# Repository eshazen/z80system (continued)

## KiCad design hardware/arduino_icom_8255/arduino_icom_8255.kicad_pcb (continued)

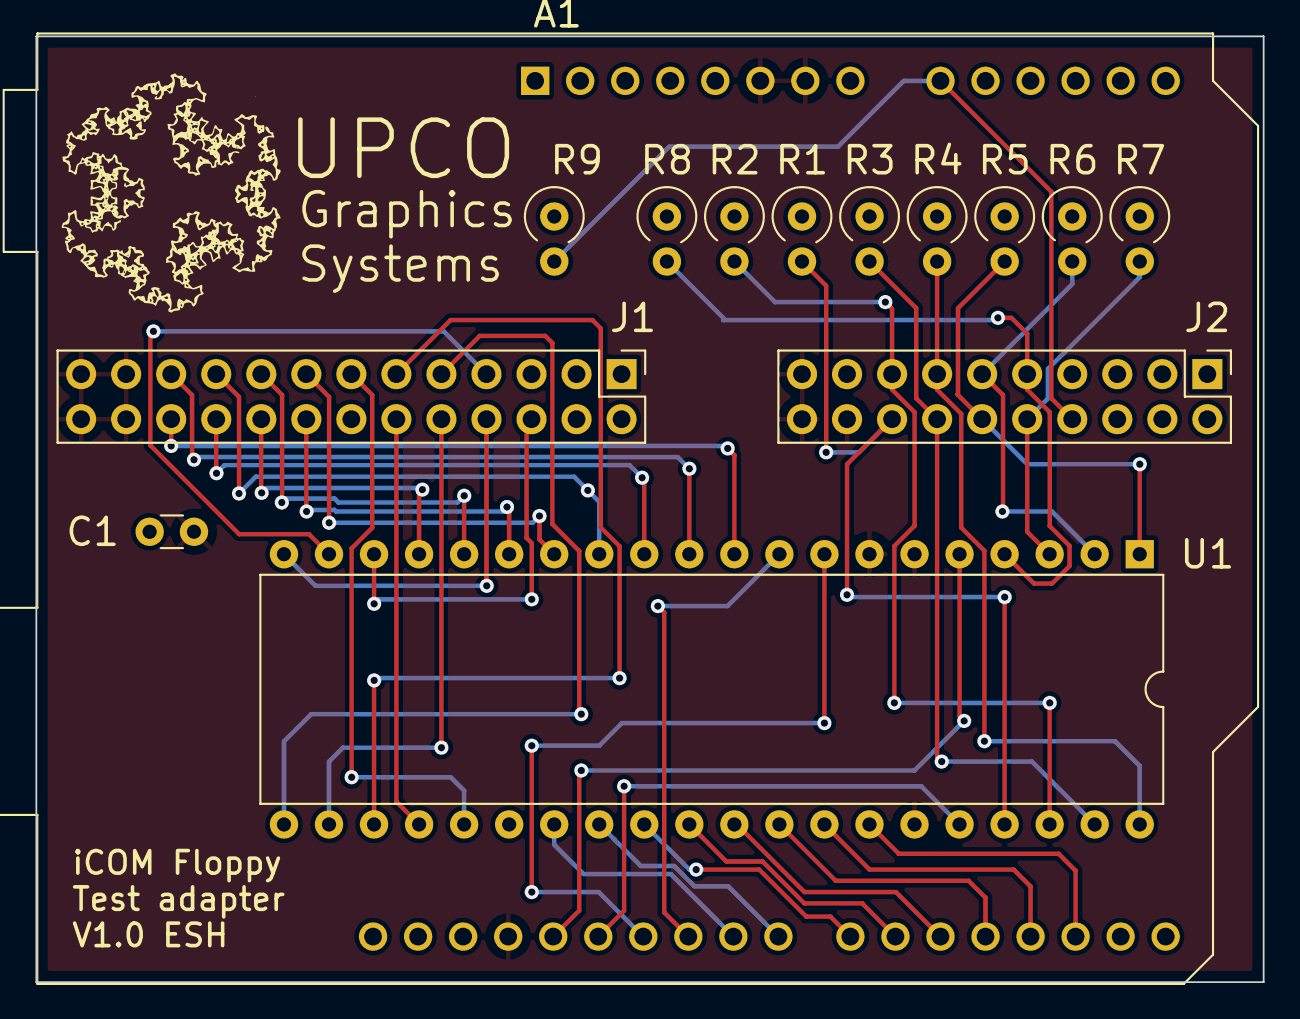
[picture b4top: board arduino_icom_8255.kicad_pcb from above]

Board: 2 copper layers, 69.2 x 53.3 mm, 14 parts (0 on the bottom side), 39 nets.

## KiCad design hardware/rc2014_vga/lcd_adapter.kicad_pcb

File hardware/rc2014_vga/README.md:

# LCD/VGA adapter for Digilent CMOD A7

This is a new RC2014 board which provides VGA display.
It can connect either to a surplus VGA LCD via flex connector
or standard VGA.

RC2014 interface via serial, with 6 pin connector for
a serial keyboard.

A possible PS/2 keyboard interface.

_Rev A Errors_

The VGA connector overlaps several resistors and C2.  This is salvageable
by either cutting away part of the VGA or mounting the other parts on the back.

It turns out that the CMOD-A7 has a built-in oscillator, so the oscillator module
and 3.3V regulator aren't needed at all, so I left them out.

Also it is *highly recommended* to put a Schottky diode in series with the power
to the CMOD-A7 so you can freely use either USB power or RC2014 power.
Plus the CMOD-A7 can take 5V directly.  I cut the trace to pin 24 of the CMOD
and soldered a diode from 5V to this pin.

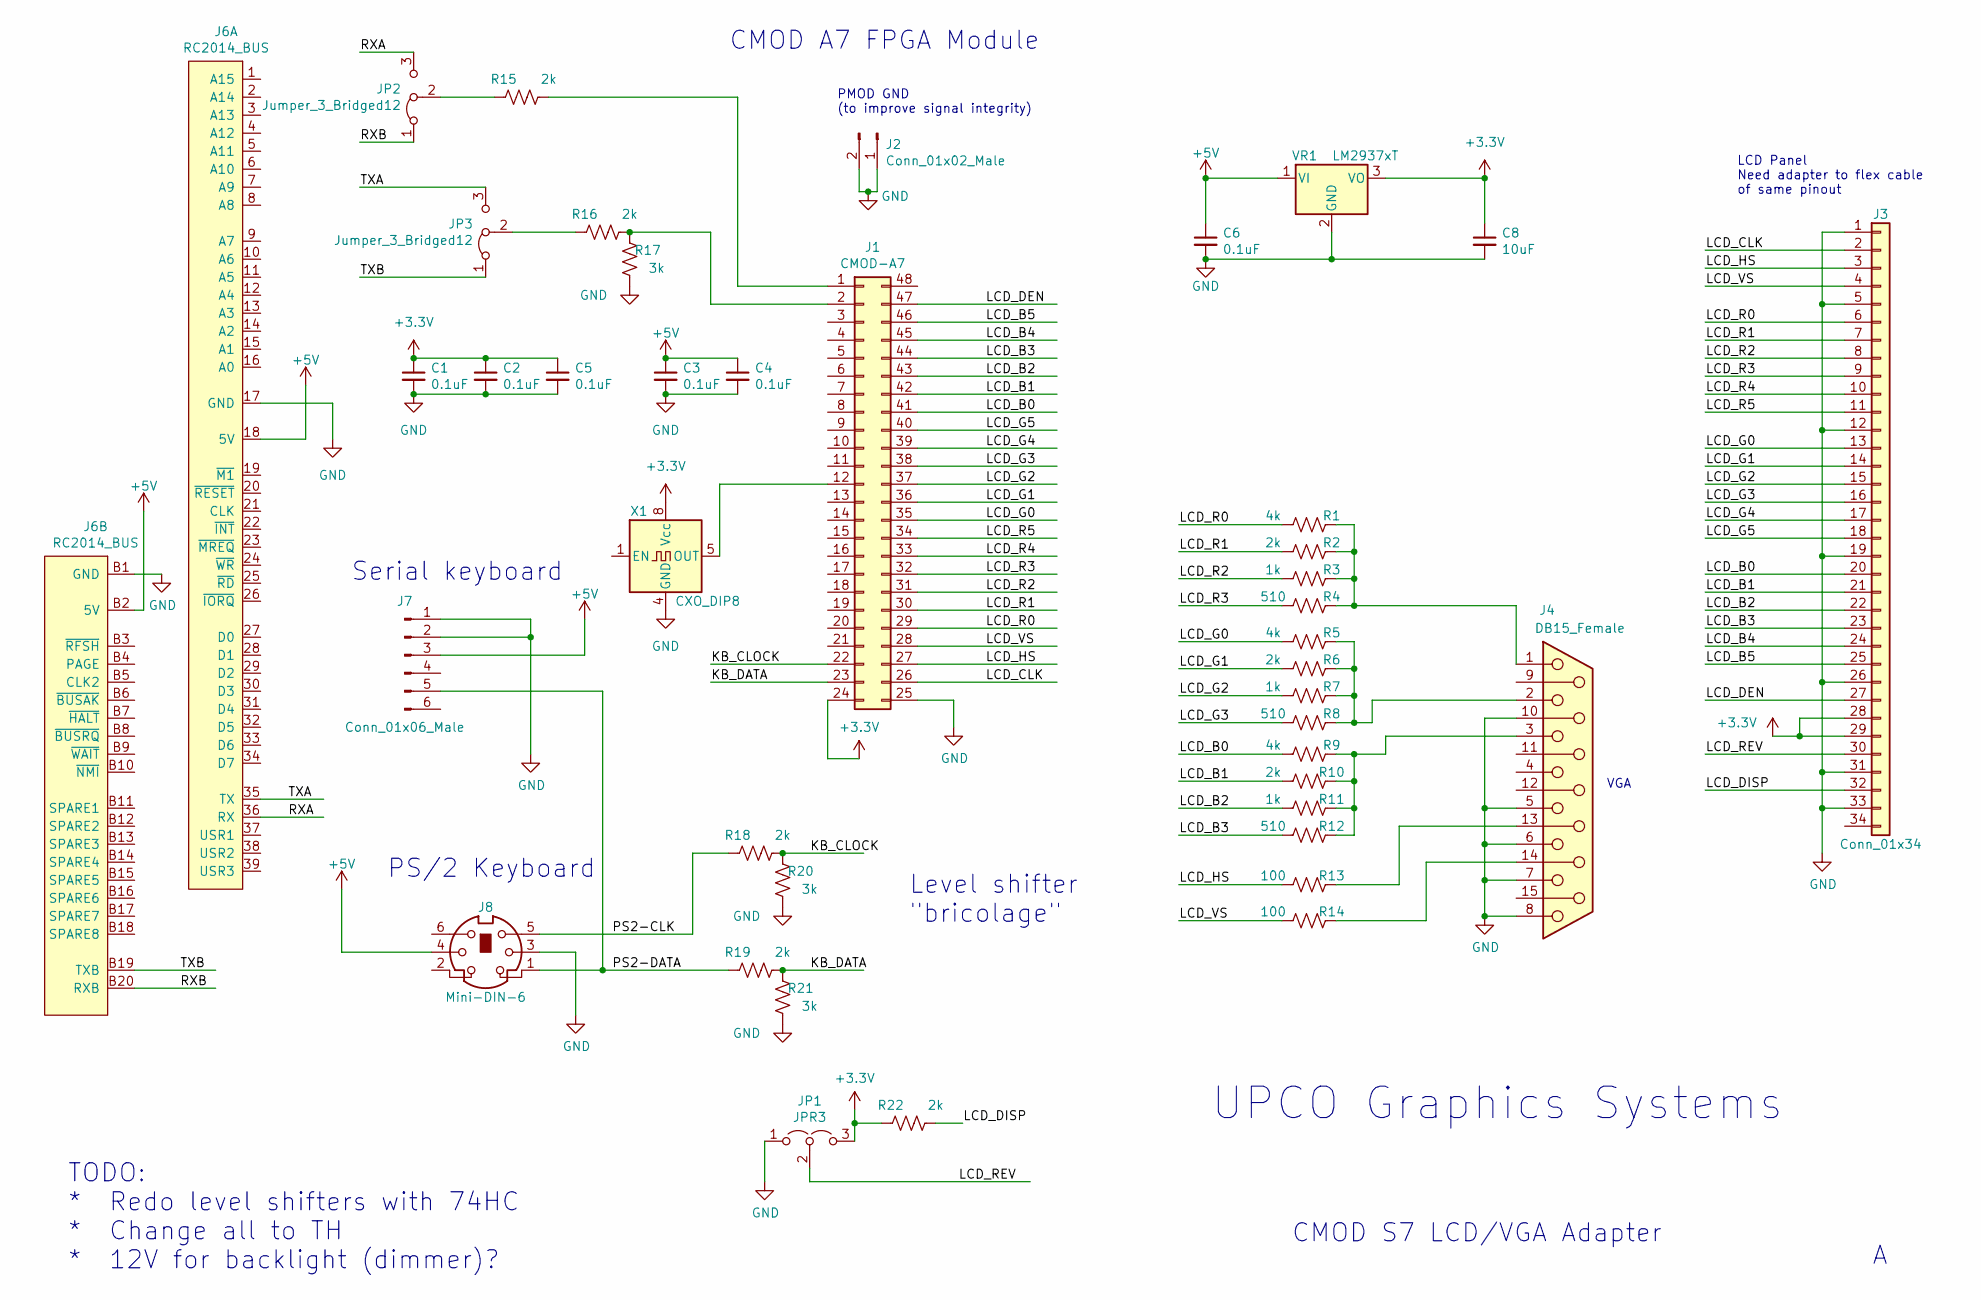
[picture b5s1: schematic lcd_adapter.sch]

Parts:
C1, C2, C3, C4, C5, C6: 0.1uF; C_Disc_D5.0mm_W2.5mm_P2.50mm
C8: 10uF; C_Disc_D5.0mm_W2.5mm_P2.50mm
J1: CMOD-A7; DIP-48_W15.24mm_Socket_LongPads
J2: Conn_01x02_Male; PinHeader_2x01_P2.54mm_Vertical
J3: Conn_01x34; PinHeader_2x17_P2.54mm_Vertical
J4: DB15_Female; DSUB-15-HD_Female_Horizontal_P2.29x1.98mm_EdgePinOffset9.40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
J6: RC2014_BUS; RC2014_Header
J7: Conn_01x06_Male; PinHeader_1x06_P2.54mm_Vertical
J8: Mini-DIN-6; PinSocket_2x03_P2.54mm_Vertical
JP1: JPR3; PinHeader_1x03_P2.54mm_Vertical
JP2, JP3: Jumper_3_Bridged12; PinSocket_1x03_P2.54mm_Vertical
R1, R5, R9: 4k; R_Axial_DIN0204_L3.6mm_D1.6mm_P2.54mm_Vertical
R2, R6, R10, R15, R16, R18, R19, R22: 2k; R_Axial_DIN0204_L3.6mm_D1.6mm_P2.54mm_Vertical
R3, R7, R11: 1k; R_Axial_DIN0204_L3.6mm_D1.6mm_P2.54mm_Vertical
R4, R8, R12: 510; R_Axial_DIN0204_L3.6mm_D1.6mm_P2.54mm_Vertical
R13, R14: 100; R_Axial_DIN0204_L3.6mm_D1.6mm_P2.54mm_Vertical
R17, R20, R21: 3k; R_Axial_DIN0204_L3.6mm_D1.6mm_P2.54mm_Vertical
VR1: LM2937xT; TO-220-3_Vertical
X1: CXO_DIP8; Oscillator_DIP-8

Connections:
+3V3: C1.1, C2.1, C5.1, C8.1, J1.24, J3.28, J3.29, JP1.3 (B), R22.2, VR1.3 (VO), X1.8 (Vcc)
+5V: C3.1, C4.1, C6.1, J6.18 (5V), J6.B2 (5V), J7.3, J8.4, VR1.1 (VI)
/KB_CLOCK: J1.22, R18.1, R20.2
/KB_DATA: J1.23, R19.1, R21.2
/LCD_B0: J1.41, J3.20, R9.2
/LCD_B1: J1.42, J3.21, R10.2
/LCD_B2: J1.43, J3.22, R11.2
/LCD_B3: J1.44, J3.23, R12.2
/LCD_B4: J1.45, J3.24
/LCD_B5: J1.46, J3.25
/LCD_CLK: J1.26, J3.2
/LCD_DEN: J1.47, J3.27
/LCD_DISP: J3.32, R22.1
/LCD_G0: J1.35, J3.13, R5.2
/LCD_G1: J1.36, J3.14, R6.2
/LCD_G2: J1.37, J3.15, R7.2
/LCD_G3: J1.38, J3.16, R8.2
/LCD_G4: J1.39, J3.17
/LCD_G5: J1.40, J3.18
/LCD_HS: J1.27, J3.3, R13.2
/LCD_R0: J1.29, J3.6, R1.2
/LCD_R1: J1.30, J3.7, R2.2
/LCD_R2: J1.31, J3.8, R3.2
/LCD_R3: J1.32, J3.9, R4.2
/LCD_R4: J1.33, J3.10
/LCD_R5: J1.34, J3.11
/LCD_REV: J3.30, JP1.2 (C)
/LCD_VS: J1.28, J3.4, R14.2
/PS2-CLK: J8.5, R18.2
/PS2-DATA: J7.5, J8.1, R19.2
/RXA: J6.36 (RX), JP2.3 (B)
/RXB: J6.B20 (RXB), JP2.1 (A)
/TXA: J6.35 (TX), JP3.3 (B)
/TXB: J6.B19 (TXB), JP3.1 (A)
GND: C1.2, C2.2, C3.2, C4.2, C5.2, C6.2, C8.2, J1.25, J2.1, J2.2, J3.1, J3.5, J3.12, J3.19, J3.26, J3.31, J3.33, J4.5, J4.6, J4.7, J4.8, J4.10, J6.17 (GND), J6.B1 (GND), J7.1, J7.2, J8.3, JP1.1 (A), R17.1, R20.1, R21.1, VR1.2 (GND), X1.4 (GND)
unnamed: J1.1, R15.1
unnamed: J1.2, R16.1, R17.2
unnamed: J1.12, X1.5 (OUT)
unnamed: J4.1, R1.1, R2.1, R3.1, R4.1
unnamed: J4.2, R5.1, R6.1, R7.1, R8.1
unnamed: J4.3, R9.1, R10.1, R11.1, R12.1
unnamed: J4.13, R13.1
unnamed: J4.14, R14.1
unnamed: JP2.2 (C), R15.2
unnamed: JP3.2 (C), R16.2

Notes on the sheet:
PMOD GND (to improve signal integrity)
LCD Panel Need adapter to flex cable of same pinout
VGA
UPCO Graphics Systems
CMOD S7 LCD/VGA Adapter
TODO: * Redo level shifters with 74HC * Change all to TH * 12V for backlight (dimmer)?
CMOD A7 FPGA Module
Serial keyboard
PS/2 Keyboard
Level shifter "bricolage"

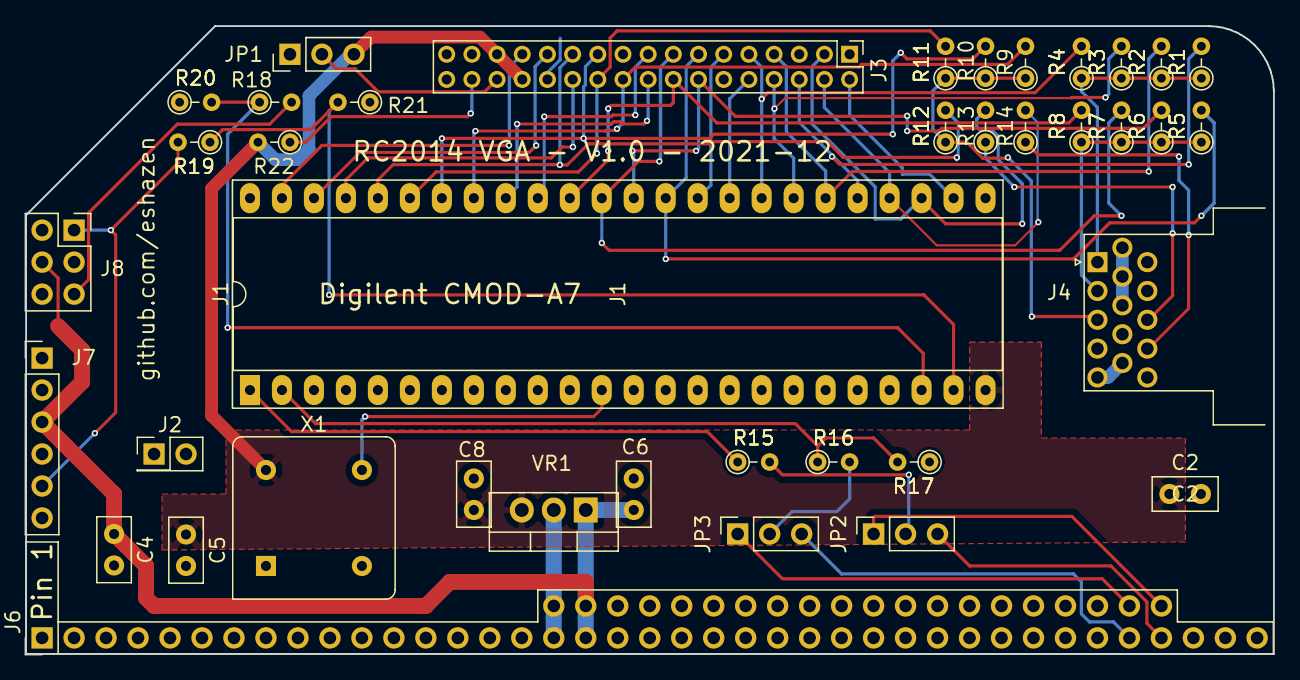
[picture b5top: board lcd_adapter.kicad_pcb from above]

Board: 2 copper layers, 99.1 x 49.9 mm, 39 parts (0 on the bottom side), 45 nets.

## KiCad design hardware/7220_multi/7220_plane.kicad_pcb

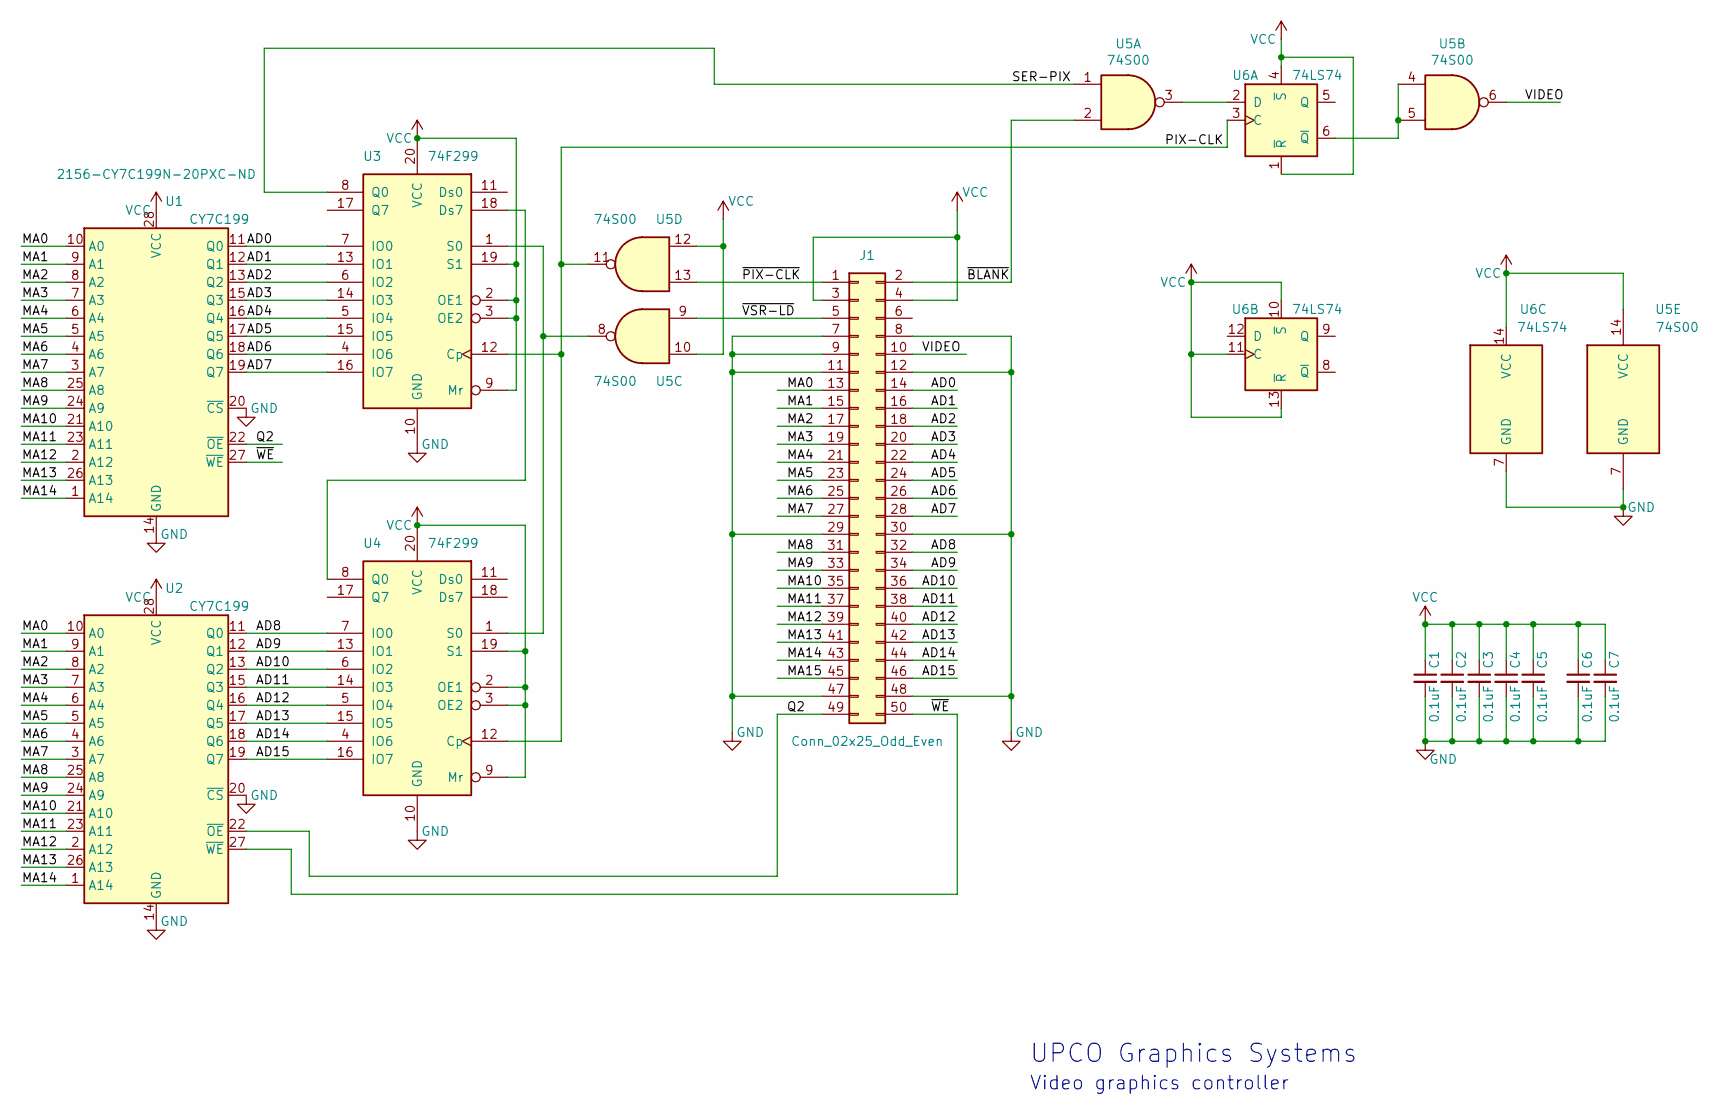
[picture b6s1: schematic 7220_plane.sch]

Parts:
C1, C2, C3, C4, C5, C6, C7: 0.1uF; C_Disc_D5.0mm_W2.5mm_P2.50mm
J1: Conn_02x25_Odd_Even; PinSocket_2x25_P2.54mm_Vertical
U1, U2: CY7C199; DIP-28_W7.62mm
U3, U4: 74F299; DIP-20_W7.62mm
U5: 74S00; DIP-14_W7.62mm
U6: 74LS74; DIP-14_W7.62mm

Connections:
/AD0: J1.14, U1.11 (Q0), U3.7 (IO0)
/AD1: J1.16, U1.12 (Q1), U3.13 (IO1)
/AD2: J1.18, U1.13 (Q2), U3.6 (IO2)
/AD3: J1.20, U1.15 (Q3), U3.14 (IO3)
/AD4: J1.22, U1.16 (Q4), U3.5 (IO4)
/AD5: J1.24, U1.17 (Q5), U3.15 (IO5)
/AD6: J1.26, U1.18 (Q6), U3.4 (IO6)
/AD7: J1.28, U1.19 (Q7), U3.16 (IO7)
/AD8: J1.32, U2.11 (Q0), U4.7 (IO0)
/AD9: J1.34, U2.12 (Q1), U4.13 (IO1)
/AD10: J1.36, U2.13 (Q2), U4.6 (IO2)
/AD11: J1.38, U2.15 (Q3), U4.14 (IO3)
/AD12: J1.40, U2.16 (Q4), U4.5 (IO4)
/AD13: J1.42, U2.17 (Q5), U4.15 (IO5)
/AD14: J1.44, U2.18 (Q6), U4.4 (IO6)
/AD15: J1.46, U2.19 (Q7), U4.16 (IO7)
/MA0: J1.13, U1.10 (A0), U2.10 (A0)
/MA1: J1.15, U1.9 (A1), U2.9 (A1)
/MA2: J1.17, U1.8 (A2), U2.8 (A2)
/MA3: J1.19, U1.7 (A3), U2.7 (A3)
/MA4: J1.21, U1.6 (A4), U2.6 (A4)
/MA5: J1.23, U1.5 (A5), U2.5 (A5)
/MA6: J1.25, U1.4 (A6), U2.4 (A6)
/MA7: J1.27, U1.3 (A7), U2.3 (A7)
/MA8: J1.31, U1.25 (A8), U2.25 (A8)
/MA9: J1.33, U1.24 (A9), U2.24 (A9)
/MA10: J1.35, U1.21 (A10), U2.21 (A10)
/MA11: J1.37, U1.23 (A11), U2.23 (A11)
/MA12: J1.39, U1.2 (A12), U2.2 (A12)
/MA13: J1.41, U1.26 (A13), U2.26 (A13)
/MA14: J1.43, U1.1 (A14), U2.1 (A14)
/MA15: J1.45
/PIX-CLK: U3.12 (Cp), U4.12 (Cp), U5.11, U6.3 (C)
/Q2: J1.49, U1.22 (~OE), U2.22 (~OE)
/SER-PIX: U3.8 (Q0), U5.1
/VIDEO: J1.10, U5.6
/~BLANK: J1.2, U5.2
/~PIX-CLK: J1.1, U5.13
/~VSR-LD: J1.5, U5.9
/~WE: J1.50, U1.27 (~WE), U2.27 (~WE)
GND: C1.2, C2.2, C3.2, C4.2, C5.2, C6.2, C7.2, J1.7, J1.8, J1.9, J1.11, J1.12, J1.29, J1.30, J1.47, J1.48, U1.14 (GND), U1.20 (~CS), U2.14 (GND), U2.20 (~CS), U3.10 (GND), U4.10 (GND), U5.7 (GND), U6.7 (GND)
unnamed: U3.1 (S0), U4.1 (S0), U5.8
unnamed: U3.18 (Ds7), U4.8 (Q0)
unnamed: U5.3, U6.2 (D)
unnamed: U5.4, U5.5, U6.6 (~Q)
VCC: C1.1, C2.1, C3.1, C4.1, C5.1, C6.1, C7.1, J1.3, J1.4, U1.28 (VCC), U2.28 (VCC), U3.2 (OE1), U3.3 (OE2), U3.9 (Mr), U3.19 (S1), U3.20 (VCC), U4.2 (OE1), U4.3 (OE2), U4.9 (Mr), U4.19 (S1), U4.20 (VCC), U5.10, U5.12, U5.14 (VCC), U6.1 (~R), U6.4 (~S), U6.10 (~S), U6.11 (C), U6.13 (~R), U6.14 (VCC)

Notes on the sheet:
UPCO Graphics Systems
Video graphics controller

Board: 2 copper layers, 14 parts (0 on the bottom side), 45 nets, no tracks yet.

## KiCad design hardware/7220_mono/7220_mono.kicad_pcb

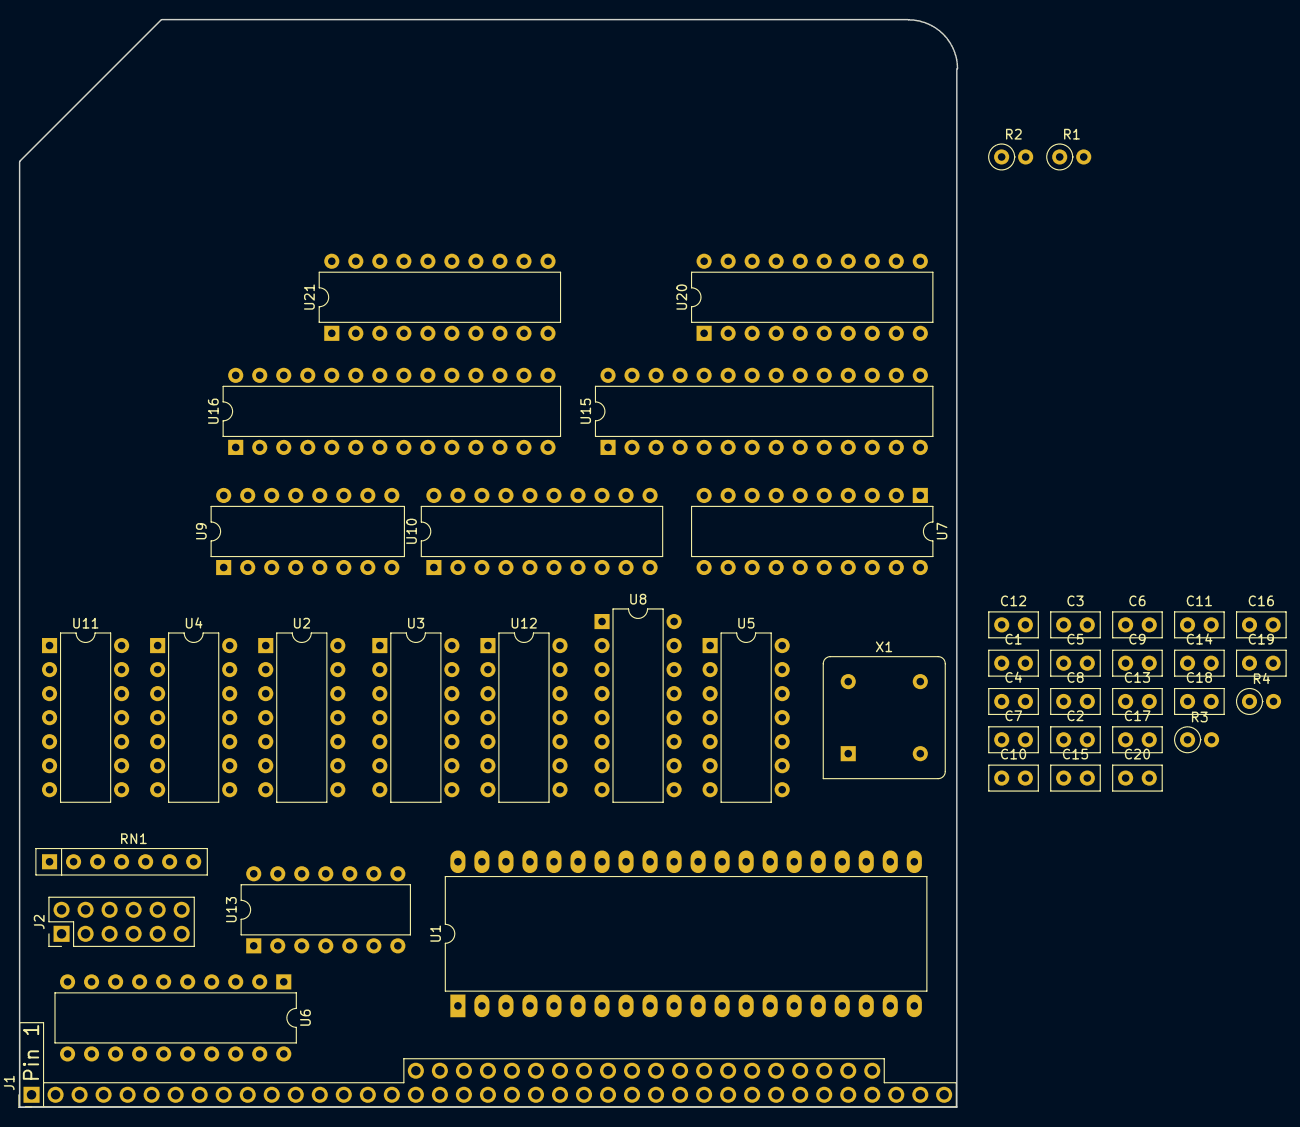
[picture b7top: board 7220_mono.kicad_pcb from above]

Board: 2 copper layers, 99.2 x 115.0 mm, 45 parts (0 on the bottom side), 87 nets, no tracks yet.

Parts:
C1, C2, C3, C4, C5, C6, C7, C8, C9, C10, C11, C12, C13, C14, C15, C16, C17, C18, C19, C20: 0.1uF; C_Disc_D5.0mm_W2.5mm_P2.50mm
J1: RC2014_BUS; RC2014_Header
J2: JUMPER; PinHeader_2x06_P2.54mm_Vertical
R1: 270; R_Axial_DIN0207_L6.3mm_D2.5mm_P2.54mm_Vertical
R2: 330; R_Axial_DIN0207_L6.3mm_D2.5mm_P2.54mm_Vertical
R3: 1.5k; R_Axial_DIN0207_L6.3mm_D2.5mm_P2.54mm_Vertical
R4: 470; R_Axial_DIN0207_L6.3mm_D2.5mm_P2.54mm_Vertical
RN1: 10k; R_Array_SIP7
U1: UPD7220; DIP-40_W15.24mm_LongPads
U2, U11: 74LS74; DIP-14_W7.62mm
U3, U5: 74AC04; DIP-14_W7.62mm
U4: 74S00; DIP-14_W7.62mm
U6: 74LS682; DIP-20_W7.62mm
U7: 74AC373; DIP-20_W7.62mm
U8: 74S163; DIP-16_W7.62mm
U9: 74S175; DIP-16_W7.62mm
U10: 74LS373; DIP-20_W7.62mm
U12: 74S20; DIP-14_W7.62mm
U13: 74LS00; DIP-14_W7.62mm
U15, U16: CY7C199; DIP-28_W7.62mm
U20, U21: 74F299; DIP-20_W7.62mm
X1: 40.000MHz; Oscillator_DIP-8

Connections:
/2xWCLK: R4.2, U1.1, U2.11, U3.10
/AD0: U1.22, U7.3, U15.11, U20.7
/AD1: U1.23, U7.4, U15.12, U20.13
/AD2: U1.24, U7.7, U15.13, U20.6
/AD3: U1.25, U7.8, U15.15, U20.14
/AD4: U1.26, U7.13, U15.16, U20.5
/AD5: U1.27, U7.14, U15.17, U20.15
/AD6: U1.28, U7.17, U15.18, U20.4
/AD7: U1.29, U7.18, U15.19, U20.16
/AD8: U1.30, U10.3, U16.11, U21.7
/AD9: U1.31, U10.4, U16.12, U21.13
/AD10: U1.32, U10.7, U16.13, U21.6
/AD11: U1.33, U10.8, U16.15, U21.14
/AD12: U1.34, U10.13, U16.16, U21.5
/AD13: U1.35, U10.14, U16.17, U21.15
/AD14: U1.36, U10.17, U16.18, U21.4
/AD15: U1.37, U10.18, U16.19, U21.16
/DBIN: U2.2, U3.6
/MA0: U7.2, U15.10, U16.10
/MA1: U7.5, U15.9, U16.9
/MA2: U7.6, U15.8, U16.8
/MA3: U7.9, U15.7, U16.7
/MA4: U7.12, U15.6, U16.6
/MA5: U7.15, U15.5, U16.5
/MA6: U7.16, U15.4, U16.4
/MA7: U7.19, U15.3, U16.3
/MA8: U10.2, U15.25, U16.25
/MA9: U10.5, U15.24, U16.24
/MA10: U10.6, U15.21, U16.21
/MA11: U10.9, U15.23, U16.23
/MA12: U10.12, U15.2, U16.2
/MA13: U10.15, U15.26, U16.26
/MA14: U10.16, U15.1, U16.1
/PIX-CLK: R1.2, R2.1, U3.4, U8.2, U11.11, U20.12, U21.12
/Q1: U2.5, U2.12
/Q2: U2.9, U4.13, U15.22, U16.22
/SER-PIX: U4.5, U20.8
/VSR-LD: U4.1, U5.8, U20.1, U21.1
/cpu_if/DB0: J1.27, U1.19
/cpu_if/DB1: J1.28, U1.18
/cpu_if/DB2: J1.29, U1.17
/cpu_if/DB3: J1.30, U1.16
/cpu_if/DB4: J1.31, U1.15
/cpu_if/DB5: J1.32, U1.14
/cpu_if/DB6: J1.33, U1.13
/cpu_if/DB7: J1.34, U1.12
/~2xWCLK: U2.3, U3.11, U4.12, U8.12, U11.3, U12.4
/~ALE: U1.6, U5.1, U7.11, U10.11, U11.2
/~BLANK: U4.4, U9.11
/~DBIN: U3.5, U5.4
/~PIX-CLK: U3.2, U3.3, U4.2
/~WE: U4.11, U15.27, U16.27
GND: C1.2, C2.2, C3.2, C4.2, C5.2, C6.2, C7.2, C8.2, C9.2, C10.2, C11.2, C12.2, C13.2, C14.2, C15.2, C16.2, C17.2, C18.2, C19.2, C20.2, J1.17, J1.B1, J2.1, J2.3, J2.5, J2.7, J2.9, J2.11, R2.2, U1.20, U1.21, U6.3, U7.10, U8.3, U8.4, U8.5, U8.8, U9.8, U10.10, U13.7, U15.14, U15.20, U16.14, U16.20, U20.10, U21.10, X1.4
unnamed: J1.9, U6.17
unnamed: J1.10, U6.15
unnamed: J1.11, U6.13
unnamed: J1.12, U6.11
unnamed: J1.13, U6.8
unnamed: J1.14, U6.6
unnamed: J1.19, U6.4
unnamed: J1.24, U13.2
unnamed: J1.25, U13.5
unnamed: J1.26, U6.2
unnamed: J2.2, RN1.2, U6.18
unnamed: J2.4, RN1.3, U6.16
unnamed: J2.6, RN1.4, U6.14
unnamed: J2.8, RN1.5, U6.12
unnamed: J2.10, RN1.6, U6.9
unnamed: J2.12, RN1.7, U6.7
unnamed: R3.1, U1.8
unnamed: U1.2, U5.3
unnamed: U1.3, U9.4
unnamed: U1.4, U9.5
unnamed: U1.5, U9.12
unnamed: U3.1, X1.5
unnamed: U3.9, U9.3
unnamed: U4.3, U9.9
unnamed: U5.11, U9.6
unnamed: U11.5, U12.5
unnamed: U5.5, U11.9
unnamed: U4.6, U11.12
unnamed: U8.14, U12.1
unnamed: U8.13, U12.2
unnamed: U5.9, U12.6
unnamed: U6.19, U13.1, U13.4
unnamed: U20.18, U21.8
VCC: C1.1, C2.1, C3.1, C4.1, C5.1, C6.1, C7.1, C8.1, C9.1, C10.1, C11.1, C12.1, C13.1, C14.1, C15.1, C16.1, C17.1, C18.1, C19.1, C20.1, J1.18, J1.B2, R1.1, R3.2, R4.1, RN1.1, U1.40, U2.1, U2.4, U2.10, U2.13, U6.5, U7.1, U7.20, U8.1, U8.6, U8.7, U8.9, U8.10, U8.16, U9.16, U10.1, U10.20, U11.1, U11.4, U11.10, U11.13, U13.14, U15.28, U20.20, U21.2, U21.3, U21.9, U21.19, U21.20, X1.8

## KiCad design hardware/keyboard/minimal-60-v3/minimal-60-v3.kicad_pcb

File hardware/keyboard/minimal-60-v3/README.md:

# Minimal 60 Keyboard

This is a KiCAD design for a retro-style minimal 60% keyboard.
Scanning is done by an ATMega128.  Interface connector is the
sparkfun/FTDI 6-pin SIP header, which is intended to provide
either 3.3V or 5V power, Tx, Rx and processor reset.

In addition there is a standard Atmel 2x3 programming header
(but see erratum).

## ECOS / Errata

* J1 (programming connector) is on the wrong side (so if soldered on the bottom where it is accessible the odd/even rows are swapped)

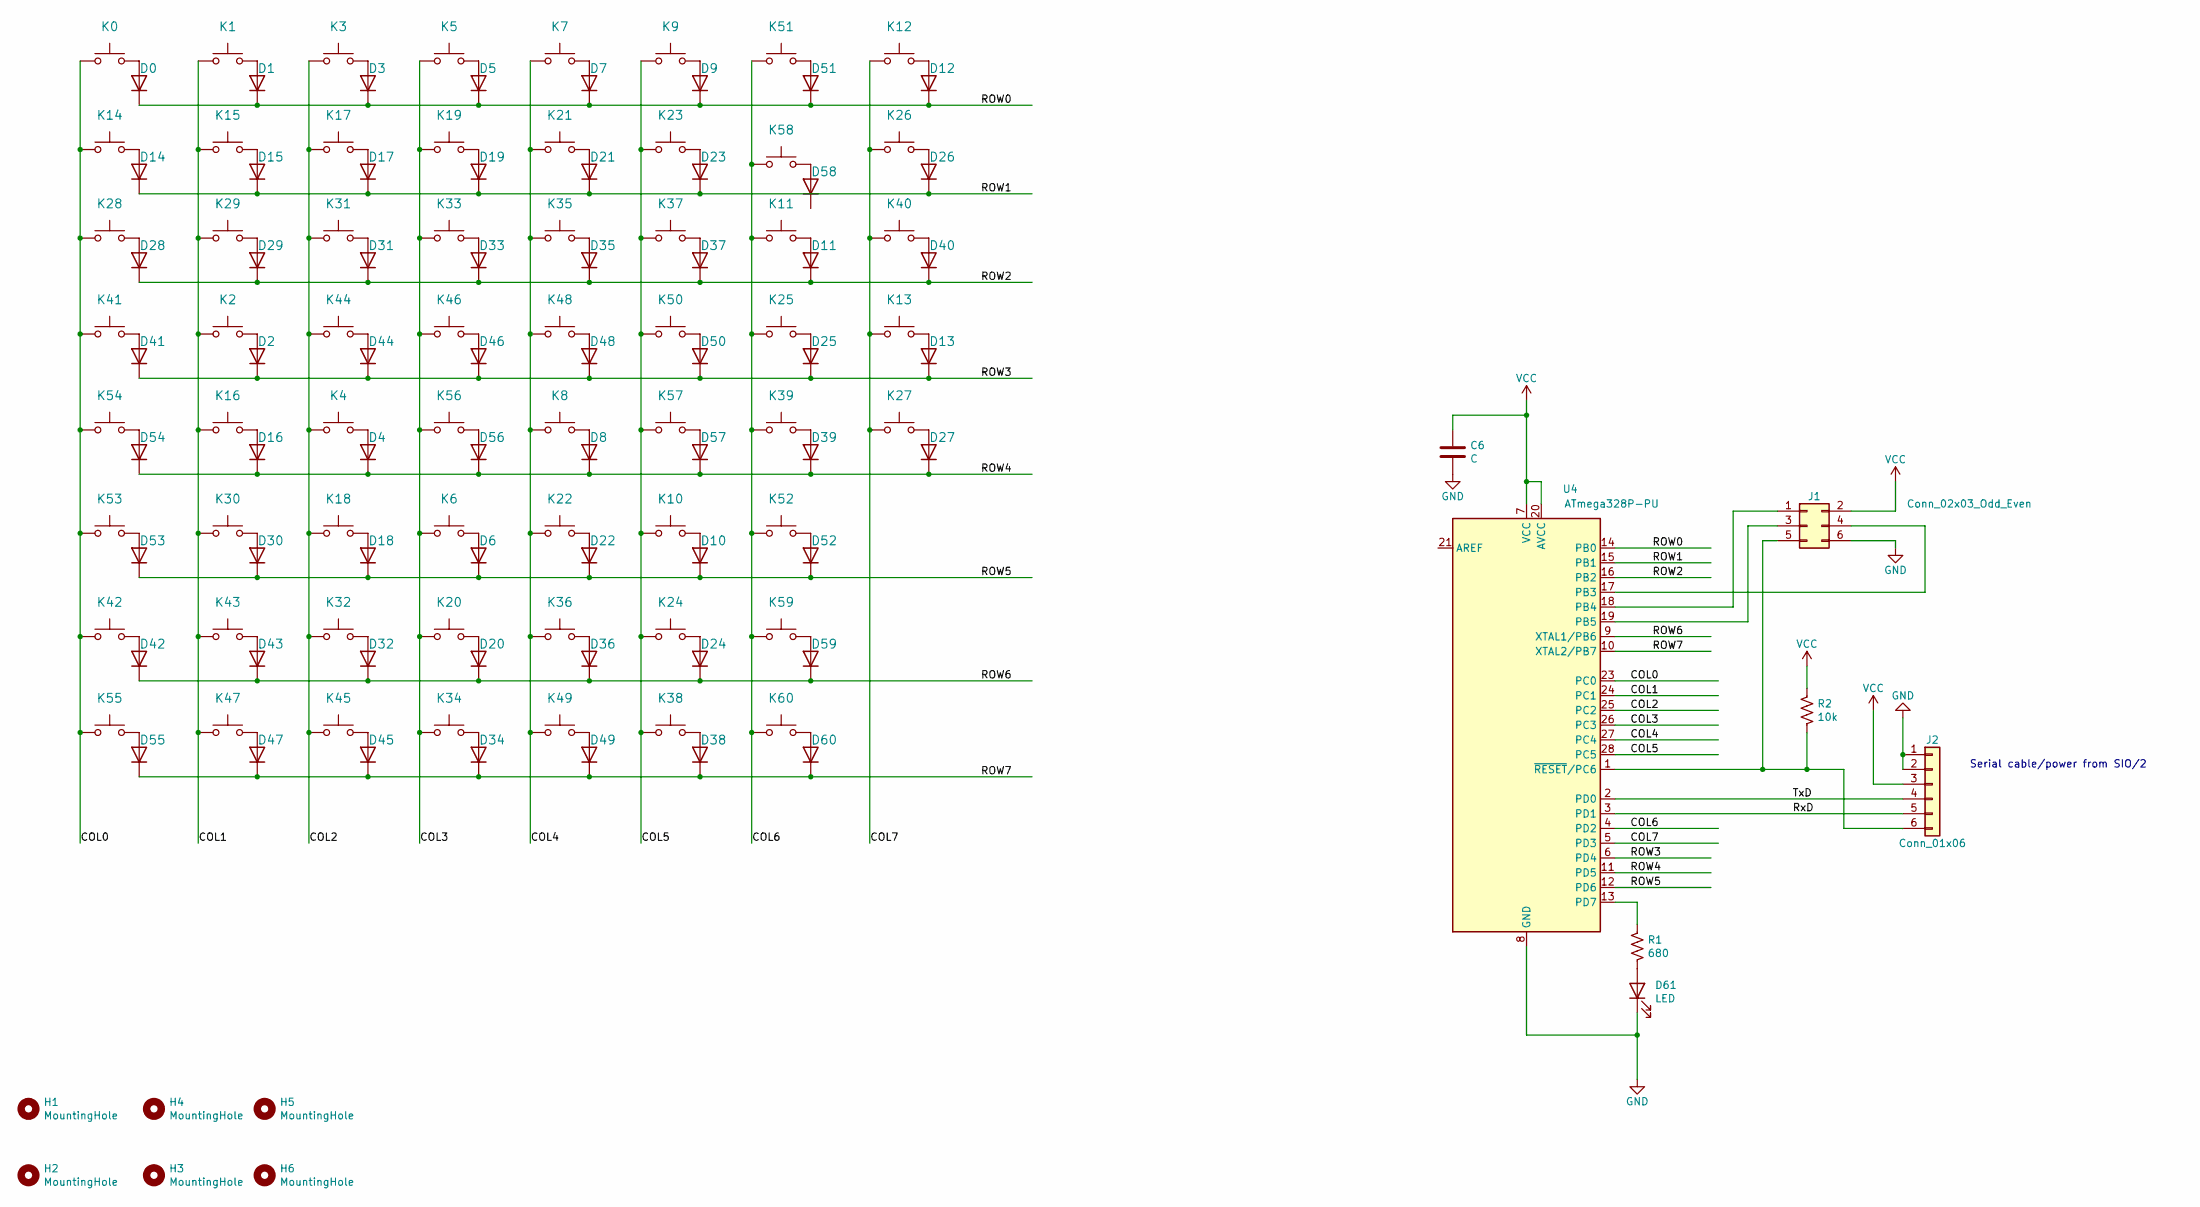
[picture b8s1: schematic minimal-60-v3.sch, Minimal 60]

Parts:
C6: C; D_DO-35_SOD27_P7.62mm_Horizontal
D0, D1, D2, D3, D4, D5, D6, D7, D8, D9, D10, D11, D12, D13, D14, D15, D16, D17, D18, D19, D20, D21, D22, D23, D24, D25, D26, D27, D28, D29, D30, D31, D32, D33, D34, D35, D36, D37, D38, D39, D40, D41, D42, D43, D44, D45, D46, D47, D48, D49, D50, D51, D52, D53, D54, D55, D56, D57, D58, D59, D60: D; D_DO-35_SOD27_P7.62mm_Horizontal
D61: LED; LED_D3.0mm
H1, H2, H3, H4, H5, H6: MountingHole; MountingHole_3.2mm_M3_DIN965
J1: Conn_02x03_Odd_Even; PinSocket_2x03_P2.54mm_Vertical
J2: Conn_01x06; PinSocket_1x06_P2.54mm_Vertical
K0, K1, K2, K3, K4, K5, K6, K7, K8, K9, K10, K11, K12, K15, K16, K17, K18, K19, K20, K21, K22, K23, K24, K25, K26, K29, K30, K31, K32, K33, K34, K35, K36, K37, K38, K39, K42, K43, K44, K45, K46, K47, K48, K49, K50, K51, K53, K58, K59, K60: KEYSW; SW_Cherry_MX_1.00u_PCB
K13: KEYSW; SW_Cherry_MX_2.00u_PCB
K14, K27, K54, K55: KEYSW; SW_Cherry_MX_1.50u_PCB
K28, K57: KEYSW; SW_Cherry_MX_1.75u_PCB
K40, K41: KEYSW; SW_Cherry_MX_2.25u_PCB
K52: KEYSW; SW_Cherry_MX_2.75u_PCB
K56: KEYSW; SW_Cherry_MX_6.25u_PCB
R1: 680; R_Axial_DIN0204_L3.6mm_D1.6mm_P7.62mm_Horizontal
R2: 10k; R_Axial_DIN0204_L3.6mm_D1.6mm_P7.62mm_Horizontal
U4: ATmega328P-PU; DIP-28_W7.62mm

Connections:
/COL0: K0.1, K14.1, K28.1, K41.1, K42.1, K53.1, K54.1, K55.1, U4.23 (PC0)
/COL1: K1.1, K2.1, K15.1, K16.1, K29.1, K30.1, K43.1, K47.1, U4.24 (PC1)
/COL2: K3.1, K4.1, K17.1, K18.1, K31.1, K32.1, K44.1, K45.1, U4.25 (PC2)
/COL3: K5.1, K6.1, K19.1, K20.1, K33.1, K34.1, K46.1, K56.1, U4.26 (PC3)
/COL4: K7.1, K8.1, K21.1, K22.1, K35.1, K36.1, K48.1, K49.1, U4.27 (PC4)
/COL5: K9.1, K10.1, K23.1, K24.1, K37.1, K38.1, K50.1, K57.1, U4.28 (PC5)
/COL6: K11.1, K25.1, K39.1, K51.1, K52.1, K58.1, K59.1, K60.1, U4.4 (PD2)
/COL7: K12.1, K13.1, K26.1, K27.1, K40.1, U4.5 (PD3)
/ROW0: D0.1 (K), D1.1 (K), D3.1 (K), D5.1 (K), D7.1 (K), D9.1 (K), D12.1 (K), D51.1 (K), U4.14 (PB0)
/ROW1: D14.1 (K), D15.1 (K), D17.1 (K), D19.1 (K), D21.1 (K), D23.1 (K), D26.1 (K), U4.15 (PB1)
/ROW2: D11.1 (K), D28.1 (K), D29.1 (K), D31.1 (K), D33.1 (K), D35.1 (K), D37.1 (K), D40.1 (K), U4.16 (PB2)
/ROW3: D2.1 (K), D13.1 (K), D25.1 (K), D41.1 (K), D44.1 (K), D46.1 (K), D48.1 (K), D50.1 (K), U4.6 (PD4)
/ROW4: D4.1 (K), D8.1 (K), D16.1 (K), D27.1 (K), D39.1 (K), D54.1 (K), D56.1 (K), D57.1 (K), U4.11 (PD5)
/ROW5: D6.1 (K), D10.1 (K), D18.1 (K), D22.1 (K), D30.1 (K), D52.1 (K), D53.1 (K), U4.12 (PD6)
/ROW6: D20.1 (K), D24.1 (K), D32.1 (K), D36.1 (K), D42.1 (K), D43.1 (K), D59.1 (K), U4.9 (XTAL1/PB6)
/ROW7: D34.1 (K), D38.1 (K), D45.1 (K), D47.1 (K), D49.1 (K), D55.1 (K), D60.1 (K), U4.10 (XTAL2/PB7)
/RxD: J2.5, U4.3 (PD1)
/TxD: J2.4, U4.2 (PD0)
GND: C6.2, D61.1 (K), J1.6, J2.1, J2.2, U4.8 (GND), U4.22 (GND)
unnamed: D0.2 (A), K0.2
unnamed: D1.2 (A), K1.2
unnamed: D2.2 (A), K2.2
unnamed: D3.2 (A), K3.2
unnamed: D4.2 (A), K4.2
unnamed: D5.2 (A), K5.2
unnamed: D6.2 (A), K6.2
unnamed: D7.2 (A), K7.2
unnamed: D8.2 (A), K8.2
unnamed: D9.2 (A), K9.2
unnamed: D10.2 (A), K10.2
unnamed: D11.2 (A), K11.2
unnamed: D12.2 (A), K12.2
unnamed: D13.2 (A), K13.2
unnamed: D14.2 (A), K14.2
unnamed: D15.2 (A), K15.2
unnamed: D16.2 (A), K16.2
unnamed: D17.2 (A), K17.2
unnamed: D18.2 (A), K18.2
unnamed: D19.2 (A), K19.2
unnamed: D20.2 (A), K20.2
unnamed: D21.2 (A), K21.2
unnamed: D22.2 (A), K22.2
unnamed: D23.2 (A), K23.2
unnamed: D24.2 (A), K24.2
unnamed: D25.2 (A), K25.2
unnamed: D26.2 (A), K26.2
unnamed: D27.2 (A), K27.2
unnamed: D28.2 (A), K28.2
unnamed: D29.2 (A), K29.2
unnamed: D30.2 (A), K30.2
unnamed: D31.2 (A), K31.2
unnamed: D32.2 (A), K32.2
unnamed: D33.2 (A), K33.2
unnamed: D34.2 (A), K34.2
unnamed: D35.2 (A), K35.2
unnamed: D36.2 (A), K36.2
unnamed: D37.2 (A), K37.2
unnamed: D38.2 (A), K38.2
unnamed: D39.2 (A), K39.2
unnamed: D40.2 (A), K40.2
unnamed: D41.2 (A), K41.2
unnamed: D42.2 (A), K42.2
unnamed: D43.2 (A), K43.2
unnamed: D44.2 (A), K44.2
unnamed: D45.2 (A), K45.2
unnamed: D46.2 (A), K46.2
unnamed: D47.2 (A), K47.2
unnamed: D48.2 (A), K48.2
unnamed: D49.2 (A), K49.2
unnamed: D50.2 (A), K50.2
unnamed: D51.2 (A), K51.2
unnamed: D52.2 (A), K52.2
unnamed: D53.2 (A), K53.2
unnamed: D54.2 (A), K54.2
unnamed: D55.2 (A), K55.2
unnamed: D56.2 (A), K56.2
unnamed: D57.2 (A), K57.2
unnamed: D58.2 (A), K58.2
unnamed: D59.2 (A), K59.2
unnamed: D60.2 (A), K60.2
unnamed: D61.2 (A), R1.2
unnamed: J1.1, U4.18 (PB4)
unnamed: J1.3, U4.19 (PB5)
unnamed: J1.4, U4.17 (PB3)
unnamed: J1.5, J2.6, R2.2, U4.1 (~RESET~/PC6)
unnamed: R1.1, U4.13 (PD7)
VCC: C6.1, J1.2, J2.3, R2.1, U4.7 (VCC), U4.20 (AVCC)

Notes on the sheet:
Serial cable/power from SIO/2

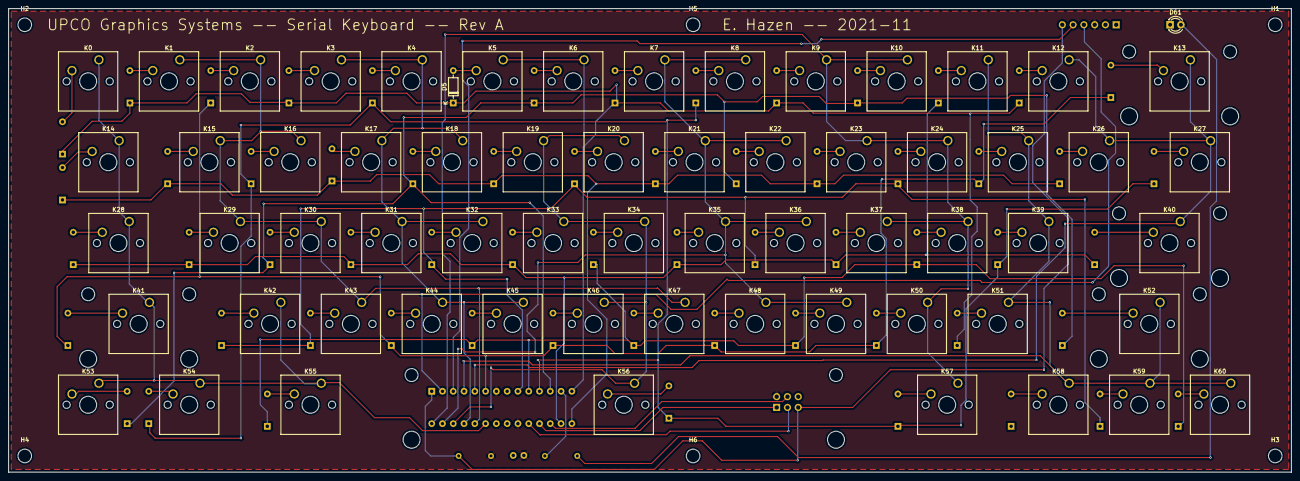
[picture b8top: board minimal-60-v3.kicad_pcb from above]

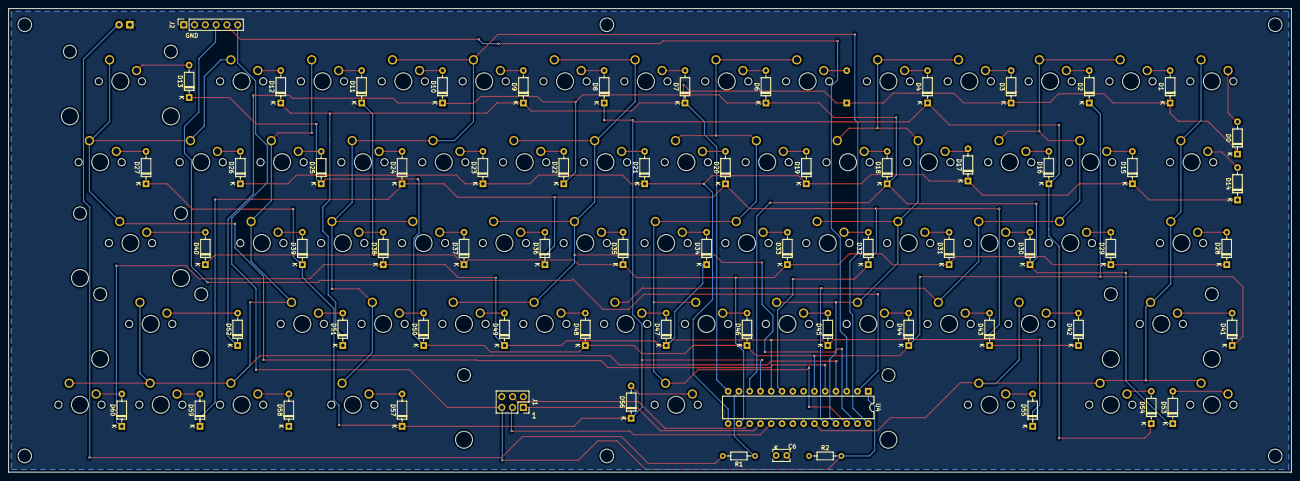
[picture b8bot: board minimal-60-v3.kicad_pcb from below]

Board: 2 copper layers, 302.3 x 109.2 mm, 135 parts (66 on the bottom side), 87 nets.

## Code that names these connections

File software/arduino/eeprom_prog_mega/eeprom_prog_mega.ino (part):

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    PORTG |= _BV(1);
  else
    PORTG &= ~_BV(1);
  if( addr & 4)			// A2 - PD7
    PORTD |= _BV(7);
  else
    PORTD &= ~_BV(7);
  if( addr & 8)			// A3 - PC1
    PORTC |= _BV(1);
  else
    PORTC &= ~_BV(1);
  if( addr & 0x10)		// A4 - PC3
    PORTC |= _BV(3);
  else
    PORTC &= ~_BV(3);
  if( addr & 0x20)		// A5 - PC5
    PORTC |= _BV(5);
  else
    PORTC &= ~_BV(5);
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    PORTL |= _BV(1);
  else
    PORTL &= ~_BV(1);
  if( dat & 8)			// D3 - PB2
    PORTB |= _BV(2);
  else
    PORTB &= ~_BV(2);
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
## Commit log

2020-07-27 Video simulation
2020-12-04 Move hardware from SVN
2020-12-04 Start LCD/VGA break for CMOD A7
2020-12-04 LCD adapter readme
2020-12-04 Schematic partly done
2020-12-04 PMOD breakout done
2020-12-09 Add README, work on bitmap mode
2020-12-11 working on memory
2020-12-11 memory
2020-12-15 Starting FPGA VGA display
2020-12-15 update mini keyboard laytou
2020-12-15 readme
2020-12-15 pics
2020-12-15 screen breakout photo
2020-12-15 rotate
2020-12-15 initial VGA design working
2020-12-15 Clone the design for RAM add
2020-12-15 starting on RAM
2020-12-19 VGA out test working on LCD+VGA
2020-12-20 working
2020-12-20 working on gitignores
2020-12-20 fixed vga
2020-12-20 working rx uart
2020-12-22 Add some keyboard-related datasheets
2020-12-22 kb files
2020-12-22 working on CPU
2020-12-30 working on 3D
2020-12-30 cleaning up
2020-12-31 update 3D
2021-09-04 small tweaks, add Motorola AN851
2021-09-05 memory wiring
2021-09-07 working on layout
2021-09-07 started routing
2021-09-08 RC2014 ideas
2021-09-19 Add RC2014 docs
2021-09-22 add 8 slot realistic backplane
2021-10-06 Simple CF test program and julia loader
2021-10-06 Port UMON to run on RC2014
2021-10-09 Collecting CP/M stuff
2021-10-09 sample CBIOS
2021-10-09 clean
2021-10-10 working on remote disk
2021-10-11 CP/M 2.2 is working!
2021-10-24 starting on IDE routines
2021-10-26 IDE read working, write has issues
2021-10-31 Fix IDE disk problem
2021-11-07 Working with 2 disks
2021-11-11 working on bios
2021-11-25 some tweaks
2021-11-30 Working on keyboard
2021-12-01 Keyboard layout done?
2021-12-08 starting KB code
2021-12-08 hex output for debug
2021-12-08 working without shift+ctrl
2021-12-09 tweaking
2021-12-09 start terminal psm
2021-12-09 starting VGA card
2021-12-09 CMOD video
2021-12-10 more cleaning
2021-12-10 more more cleaning
2021-12-10 still cleaning
2021-12-10 Change all to TH
2021-12-10 routing
2021-12-11 It seems to be working now
2021-12-11 clean up
2021-12-11 Revert "clean up"
    This reverts commit 8c1872a856aae71767773a52232689fac2f5c7a1.
2021-12-11 As built pcb
2021-12-11 start case design
2021-12-13 Removing old VGA tree, now in own repo
2021-12-21 Various CBIOS fixes
2021-12-21 save that hex file
2021-12-29 small updates
2021-12-30 Working on 7220
2022-01-09 Working on 2-board 7220
2022-01-12 working on KB plate
2022-10-02 working on new Ponoko case
2022-10-02 Adding tabs
2022-10-05 new case
2023-08-24 CPU to KiCAD 7, fix a few minor typos
2023-08-25 update all
2023-08-27 Add some iCOM docs
2023-08-27 Arduino iCOM interface
2023-08-27 As built arduino icom 1.0
2023-09-04 notes
2023-09-05 Add arduino 8255 test
2024-08-08 pushing develop
2024-08-09 New EEPROM programmer for Arduino Mega 2560
2024-08-18 EEPROM shield as built, arduino code to drive
2024-08-24 working on z180 sch
2024-08-30 schem work
2024-08-30 schematic ~ done
2024-08-30 tentative placement
2024-09-01 placement
2024-09-06 add VR
2024-09-09 tweaking placement
2025-08-21 small tweaks to placement
2025-08-21 placement complete
2025-08-21 demo routing, highlight high current nets
2025-08-26 updating
